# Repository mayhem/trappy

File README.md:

# trappy
Trappy, the mobile hippie trap

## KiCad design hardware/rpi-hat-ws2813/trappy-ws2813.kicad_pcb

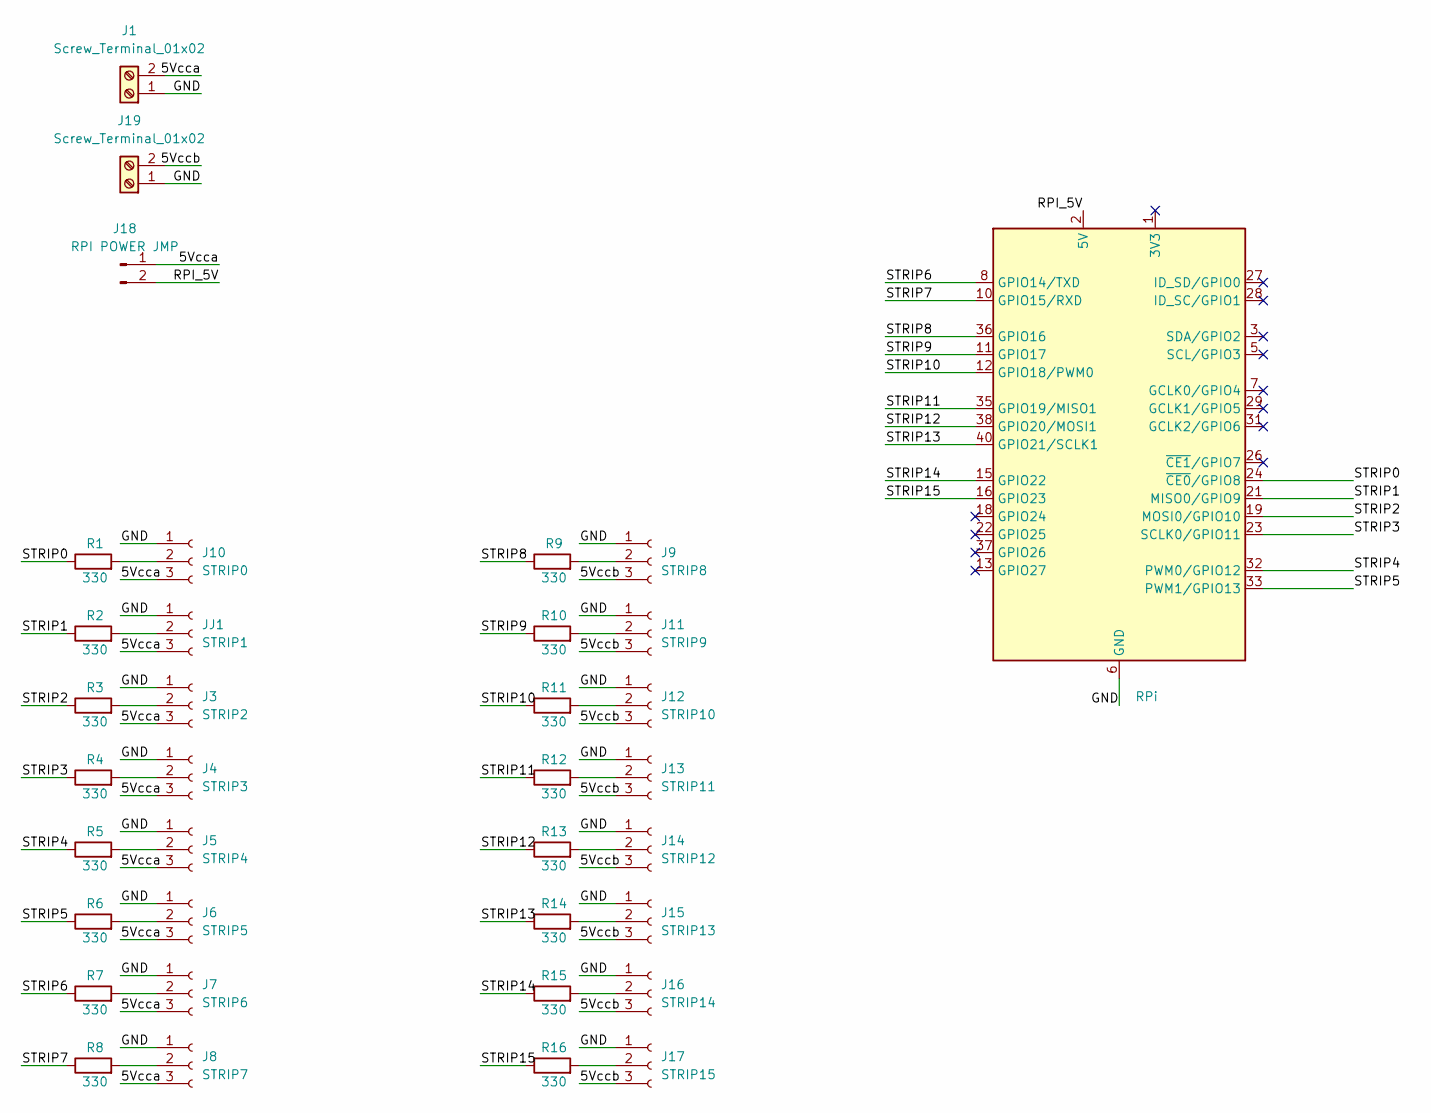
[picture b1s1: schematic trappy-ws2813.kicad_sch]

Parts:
J1, J19: Screw_Terminal_01x02; TerminalBlock_bornier-2_P5.08mm
J2: RPi; PinHeader_2x20_P2.54mm_Vertical
J3: STRIP2; JST_EH_B3B-EH-A_1x03_P2.50mm_Vertical
J4: STRIP3; JST_EH_B3B-EH-A_1x03_P2.50mm_Vertical
J5: STRIP4; JST_EH_B3B-EH-A_1x03_P2.50mm_Vertical
J6: STRIP5; JST_EH_B3B-EH-A_1x03_P2.50mm_Vertical
J7: STRIP6; JST_EH_B3B-EH-A_1x03_P2.50mm_Vertical
J8: STRIP7; JST_EH_B3B-EH-A_1x03_P2.50mm_Vertical
J9: STRIP8; JST_EH_B3B-EH-A_1x03_P2.50mm_Vertical
J10: STRIP0; JST_EH_B3B-EH-A_1x03_P2.50mm_Vertical
J11: STRIP9; JST_EH_B3B-EH-A_1x03_P2.50mm_Vertical
J12: STRIP10; JST_EH_B3B-EH-A_1x03_P2.50mm_Vertical
J13: STRIP11; JST_EH_B3B-EH-A_1x03_P2.50mm_Vertical
J14: STRIP12; JST_EH_B3B-EH-A_1x03_P2.50mm_Vertical
J15: STRIP13; JST_EH_B3B-EH-A_1x03_P2.50mm_Vertical
J16: STRIP14; JST_EH_B3B-EH-A_1x03_P2.50mm_Vertical
J17: STRIP15; JST_EH_B3B-EH-A_1x03_P2.50mm_Vertical
J18: RPI POWER JMP; PinHeader_1x02_P2.54mm_Vertical
JJ1: STRIP1; JST_EH_B3B-EH-A_1x03_P2.50mm_Vertical
R1, R2, R3, R4, R5, R6, R7, R8, R9, R10, R11, R12, R13, R14, R15, R16: 330; R_0805_2012Metric

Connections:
/5Vcca: J1.2, J3.3, J4.3, J5.3, J6.3, J7.3, J8.3, J10.3, J18.1, JJ1.3
/5Vccb: J9.3, J11.3, J12.3, J13.3, J14.3, J15.3, J16.3, J17.3, J19.2
/GND: J1.1, J2.6 (GND), J2.9 (GND), J2.14 (GND), J2.20 (GND), J2.25 (GND), J2.30 (GND), J2.34 (GND), J2.39 (GND), J3.1, J4.1, J5.1, J6.1, J7.1, J8.1, J9.1, J10.1, J11.1, J12.1, J13.1, J14.1, J15.1, J16.1, J17.1, J19.1, JJ1.1
/RPI_5V: J2.2 (5V), J2.4 (5V), J18.2
/STRIP0: J2.24 (~CE0/GPIO8), R1.1
/STRIP1: J2.21 (MISO0/GPIO9), R2.1
/STRIP2: J2.19 (MOSI0/GPIO10), R3.1
/STRIP3: J2.23 (SCLK0/GPIO11), R4.1
/STRIP4: J2.32 (PWM0/GPIO12), R5.1
/STRIP5: J2.33 (PWM1/GPIO13), R6.1
/STRIP6: J2.8 (GPIO14/TXD), R7.1
/STRIP7: J2.10 (GPIO15/RXD), R8.1
/STRIP8: J2.36 (GPIO16), R9.1
/STRIP9: J2.11 (GPIO17), R10.1
/STRIP10: J2.12 (GPIO18/PWM0), R11.1
/STRIP11: J2.35 (GPIO19/MISO1), R12.1
/STRIP12: J2.38 (GPIO20/MOSI1), R13.1
/STRIP13: J2.40 (GPIO21/SCLK1), R14.1
/STRIP14: J2.15 (GPIO22), R15.1
/STRIP15: J2.16 (GPIO23), R16.1
unnamed: J3.2, R3.2
unnamed: J4.2, R4.2
unnamed: J5.2, R5.2
unnamed: J6.2, R6.2
unnamed: J7.2, R7.2
unnamed: J8.2, R8.2
unnamed: J9.2, R9.2
unnamed: J10.2, R1.2
unnamed: J11.2, R10.2
unnamed: J12.2, R11.2
unnamed: J13.2, R12.2
unnamed: J14.2, R13.2
unnamed: J15.2, R14.2
unnamed: J16.2, R15.2
unnamed: J17.2, R16.2
unnamed: JJ1.2, R2.2

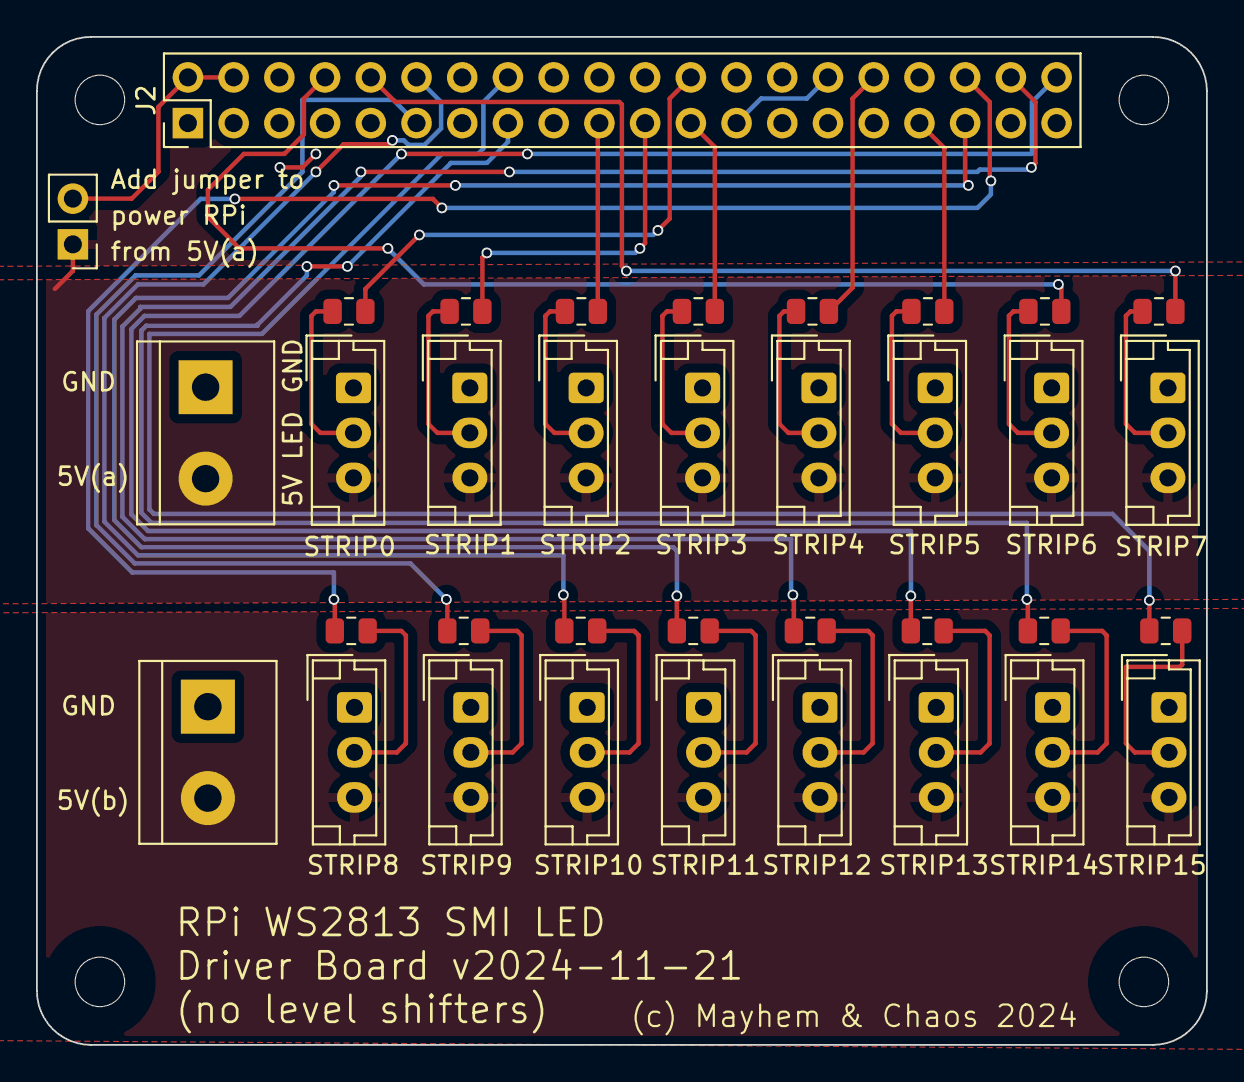
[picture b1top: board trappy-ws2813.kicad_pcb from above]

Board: 2 copper layers, 65.0 x 56.0 mm, 36 parts (0 on the bottom side), 36 nets.

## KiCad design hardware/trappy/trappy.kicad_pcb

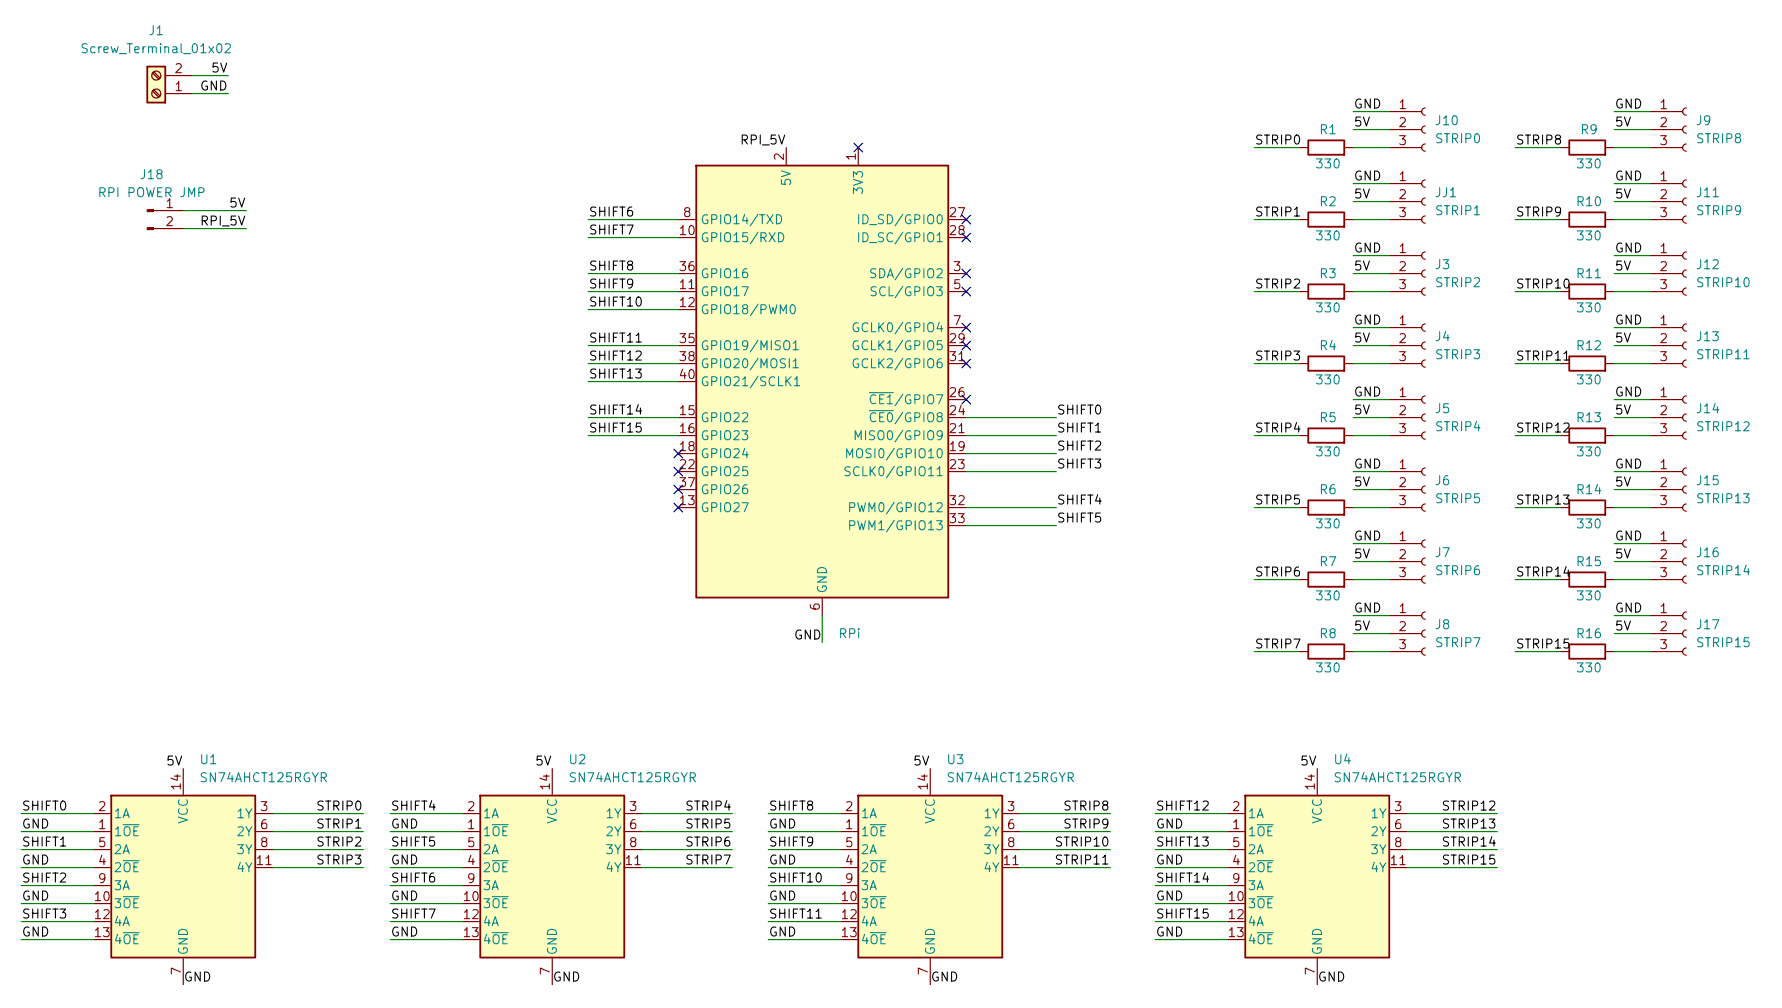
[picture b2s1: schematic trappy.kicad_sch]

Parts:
J1: Screw_Terminal_01x02; TerminalBlock_WAGO_236-102_1x02_P5.00mm_45Degree
J2: RPi; PinHeader_2x20_P2.54mm_Vertical
J3: STRIP2; JST_EH_B3B-EH-A_1x03_P2.50mm_Vertical
J4: STRIP3; JST_EH_B3B-EH-A_1x03_P2.50mm_Vertical
J5: STRIP4; JST_EH_B3B-EH-A_1x03_P2.50mm_Vertical
J6: STRIP5; JST_EH_B3B-EH-A_1x03_P2.50mm_Vertical
J7: STRIP6; JST_EH_B3B-EH-A_1x03_P2.50mm_Vertical
J8: STRIP7; JST_EH_B3B-EH-A_1x03_P2.50mm_Vertical
J9: STRIP8; JST_EH_B3B-EH-A_1x03_P2.50mm_Vertical
J10: STRIP0; JST_EH_B3B-EH-A_1x03_P2.50mm_Vertical
J11: STRIP9; JST_EH_B3B-EH-A_1x03_P2.50mm_Vertical
J12: STRIP10; JST_EH_B3B-EH-A_1x03_P2.50mm_Vertical
J13: STRIP11; JST_EH_B3B-EH-A_1x03_P2.50mm_Vertical
J14: STRIP12; JST_EH_B3B-EH-A_1x03_P2.50mm_Vertical
J15: STRIP13; JST_EH_B3B-EH-A_1x03_P2.50mm_Vertical
J16: STRIP14; JST_EH_B3B-EH-A_1x03_P2.50mm_Vertical
J17: STRIP15; JST_EH_B3B-EH-A_1x03_P2.50mm_Vertical
J18: RPI POWER JMP; PinHeader_1x02_P2.54mm_Vertical
JJ1: STRIP1; JST_EH_B3B-EH-A_1x03_P2.50mm_Vertical
R1, R2, R3, R4, R5, R6, R7, R8, R9, R10, R11, R12, R13, R14, R15, R16: 330; R_0805_2012Metric
U1, U2, U3, U4: SN74AHCT125RGYR; Texas_S-PVQFN-N14

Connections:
/5V: J1.2, J3.2, J4.2, J5.2, J6.2, J7.2, J8.2, J9.2, J10.2, J11.2, J12.2, J13.2, J14.2, J15.2, J16.2, J17.2, J18.1, JJ1.2, U1.14 (VCC), U2.14 (VCC), U3.14 (VCC), U4.14 (VCC)
/GND: J1.1, J2.6 (GND), J2.9 (GND), J2.14 (GND), J2.20 (GND), J2.25 (GND), J2.30 (GND), J2.34 (GND), J2.39 (GND), J3.1, J4.1, J5.1, J6.1, J7.1, J8.1, J9.1, J10.1, J11.1, J12.1, J13.1, J14.1, J15.1, J16.1, J17.1, JJ1.1, U1.1 (1~OE), U1.4 (2~OE), U1.7 (GND), U1.10 (3~OE), U1.13 (4~OE), U2.1 (1~OE), U2.4 (2~OE), U2.7 (GND), U2.10 (3~OE), U2.13 (4~OE), U3.1 (1~OE), U3.4 (2~OE), U3.7 (GND), U3.10 (3~OE), U3.13 (4~OE), U4.1 (1~OE), U4.4 (2~OE), U4.7 (GND), U4.10 (3~OE), U4.13 (4~OE)
/RPI_5V: J2.2 (5V), J2.4 (5V), J18.2
/SHIFT0: J2.24 (~CE0/GPIO8), U1.2 (1A)
/SHIFT1: J2.21 (MISO0/GPIO9), U1.5 (2A)
/SHIFT2: J2.19 (MOSI0/GPIO10), U1.9 (3A)
/SHIFT3: J2.23 (SCLK0/GPIO11), U1.12 (4A)
/SHIFT4: J2.32 (PWM0/GPIO12), U2.2 (1A)
/SHIFT5: J2.33 (PWM1/GPIO13), U2.5 (2A)
/SHIFT6: J2.8 (GPIO14/TXD), U2.9 (3A)
/SHIFT7: J2.10 (GPIO15/RXD), U2.12 (4A)
/SHIFT8: J2.36 (GPIO16), U3.2 (1A)
/SHIFT9: J2.11 (GPIO17), U3.5 (2A)
/SHIFT10: J2.12 (GPIO18/PWM0), U3.9 (3A)
/SHIFT11: J2.35 (GPIO19/MISO1), U3.12 (4A)
/SHIFT12: J2.38 (GPIO20/MOSI1), U4.2 (1A)
/SHIFT13: J2.40 (GPIO21/SCLK1), U4.5 (2A)
/SHIFT14: J2.15 (GPIO22), U4.9 (3A)
/SHIFT15: J2.16 (GPIO23), U4.12 (4A)
/STRIP0: R1.1, U1.3 (1Y)
/STRIP1: R2.1, U1.6 (2Y)
/STRIP2: R3.1, U1.8 (3Y)
/STRIP3: R4.1, U1.11 (4Y)
/STRIP4: R5.1, U2.3 (1Y)
/STRIP5: R6.1, U2.6 (2Y)
/STRIP6: R7.1, U2.8 (3Y)
/STRIP7: R8.1, U2.11 (4Y)
/STRIP8: R9.1, U3.3 (1Y)
/STRIP9: R10.1, U3.6 (2Y)
/STRIP10: R11.1, U3.8 (3Y)
/STRIP11: R12.1, U3.11 (4Y)
/STRIP12: R13.1, U4.3 (1Y)
/STRIP13: R14.1, U4.6 (2Y)
/STRIP14: R15.1, U4.8 (3Y)
/STRIP15: R16.1, U4.11 (4Y)
unnamed: J3.3, R3.2
unnamed: J4.3, R4.2
unnamed: J5.3, R5.2
unnamed: J6.3, R6.2
unnamed: J7.3, R7.2
unnamed: J8.3, R8.2
unnamed: J9.3, R9.2
unnamed: J10.3, R1.2
unnamed: J11.3, R10.2
unnamed: J12.3, R11.2
unnamed: J13.3, R12.2
unnamed: J14.3, R13.2
unnamed: J15.3, R14.2
unnamed: J16.3, R15.2
unnamed: J17.3, R16.2
unnamed: JJ1.3, R2.2

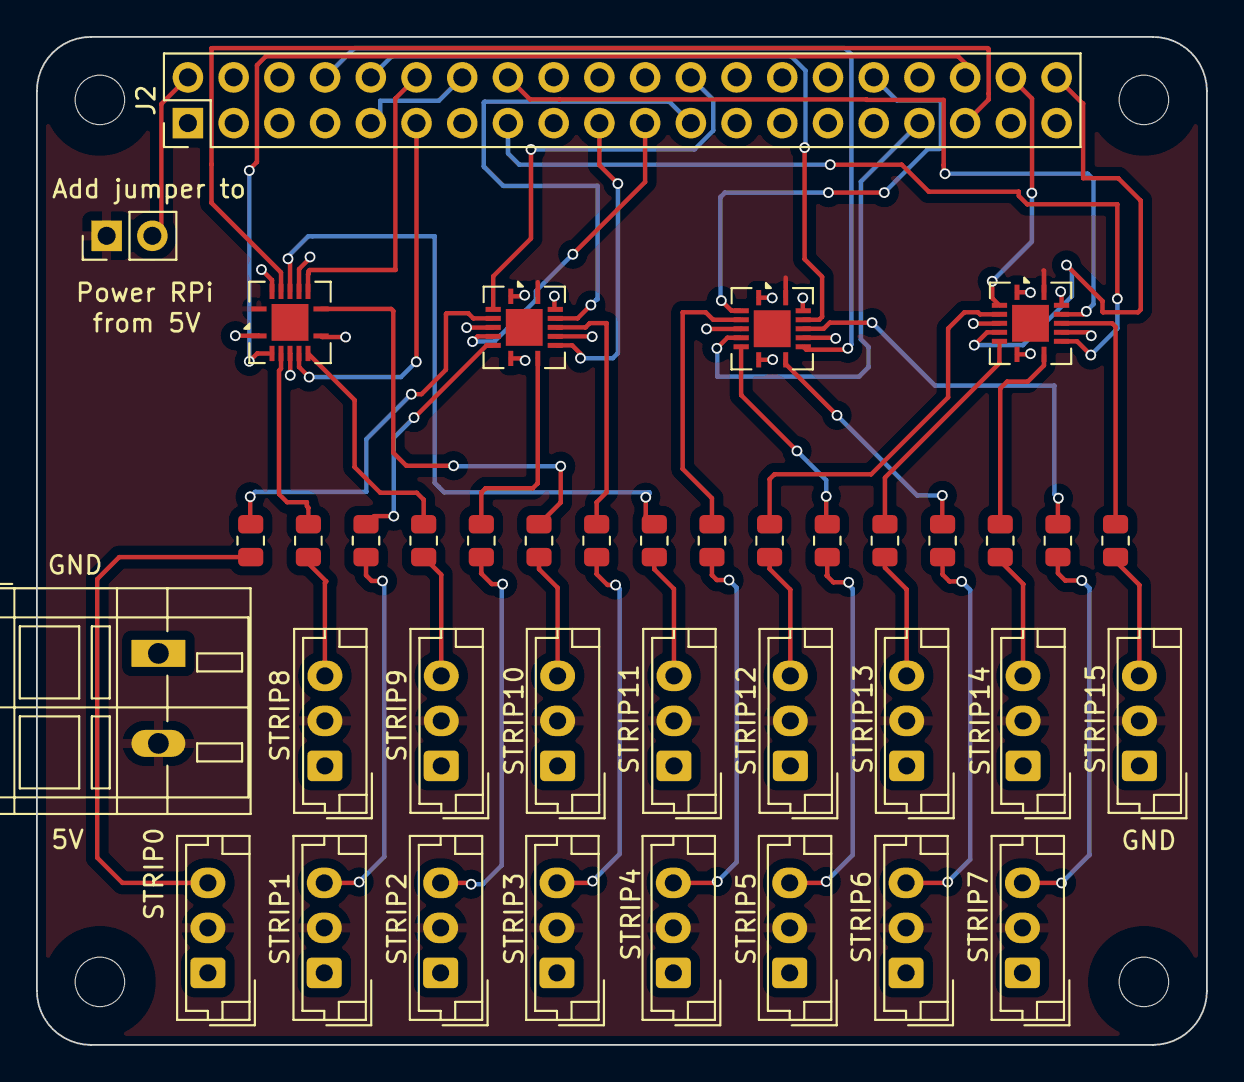
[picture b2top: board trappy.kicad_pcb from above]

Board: 2 copper layers, 65.0 x 56.0 mm, 39 parts (0 on the bottom side), 51 nets.

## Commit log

2024-04-12 First commit!
2024-04-12 New driver is working!
2024-04-12 Add in
2024-04-13 Generally working, but still strangely slow
2024-04-14 Fully debugged test case in place!
2024-04-22 Gateway code
2024-04-22 Gradients work
2024-04-22 Basic hippie trap operational. Not great, but working.
2024-04-24 The shift function works and is debugged.
2024-04-25 New system finally debugged
2024-04-25 MOre stuff is working!
2024-05-01 Break into more modules
2024-05-01 Gradient palletes are working, everything finally debugged.
2024-05-07 Finally adding python effects!
2024-05-07 Interim checkin
2024-05-07 NERDVANA!
2024-05-07 Loking really promising!
2024-05-08 scoller ported and working
2024-05-08 Starting work on a gradient scroller
2024-05-09 Gradient chase working
2024-05-09 More gradients
2024-05-09 More tweaks prior to vidalia
2024-05-10 Make gradient scroller go inward
2024-05-10 Improve gradient scroller
2024-05-16 Start work on hardware for trappy
2024-05-17 Looking pretty good!
2024-05-22 Check in latest trappy board, awaiting the board from china
2024-05-28 Fix silkscreen
2024-06-04 Changes from vidalia
2024-07-09 Add APC mini rainbow keypad setting.
2024-07-10 Now for a workable baseline
2024-07-10 Color selection working, custom colors being stored.
2024-07-11 HSV implemented in a cool way, but horrible ux
2024-07-11 HSV almost working. again.
2024-07-11 HSV is actually working, time to connec to the hippie trap
2024-07-12 time to connect to trappy!
2024-07-12 APC connected, now to drive patterns
2024-07-14 APC is controlling things!
2024-08-05 gamma correction improvements
2024-08-24 Now using prod smileds!
2024-08-25 REwriting the scroller guts
2024-08-25 A much improved gradient scroller is done.
2024-08-25 forward and reverse now work
2024-08-25 Speed control is sloppily implemented
2024-08-27 Dynamic gamma correction implemented!
2024-08-27 Clearing custom colors works
2024-08-27 Making great UI progress
2024-08-27 Getting snazzy
2024-08-27 Really coming together now!
2024-08-28 Drop duplicate events for a more responsive UI
2024-08-28 Some bugs remain, but everything is improving
2024-08-29 Particle system is cool and working!
2024-08-29 Looking pretty with max particles
2024-08-29 direction implemented
2024-08-29 Moved speed and direction setting to base effect class
2024-08-29 Instant colors -> instant hit!
2024-08-29 Get the checkerboard back in, but still buggy in live color changes
2024-08-30 Two gripes fixed
2024-09-01 Fix minor crash
2024-09-01 Particle count slider now works correctly.
2024-09-05 Add function to wait for apc mini to be connected
2024-09-05 Start stop trappy based on APC being plugged in
2024-09-08 Add sparkle effect
2024-09-08 Simplfying fader handling to be more central in effect base class
2024-09-08 Sparkles now can set the fade constant
2024-09-08 Add sweep pattern. a bit confusing and lacking color interaction
2024-09-09 Move delay logic to effect base class
2024-09-09 Add sprite support to particle system. It doesn't feel intuitive, but its not bad either.
2024-09-09 Making the particle system much more complex -- this will be really cool!
2024-09-10 Light up track and scene buttons
2024-10-20 Paging of screens implemented
2024-10-20 Getting closer to having lots of effects options!
2024-10-20 Getting fun!
2024-10-20 Support for effects screen and variant selection is working!
2024-10-20 Make the first variant suck less
2024-10-24 improve render_led to allow both directions. other simplifications.
2024-10-24 Minor improvements here and there
2024-10-24 Three distinct dot effects, done!
2024-11-06 Try a new easier to use gradient
2024-11-12 Sweep pattern is now not awful
2024-11-12 Just messing around, will find something good soon
2024-11-12 Sweep no longer sucks!
2024-11-18 Add rainbow sweep
2024-11-21 Add ws2813 board with improved power planes
2024-11-24 Banged out several more sweep block patterns
2024-11-27 Start adding drop-in
2024-11-27 Added brightness support
2024-11-27 Fix one crash
2024-12-29 Add pyusb
2024-12-29 Move defs.py to config.py
2024-12-29 Ignore buttons pressed for non-existent variants
2024-12-29 Change disconnect pad to exit the app. Also pressing "stop all clips" 5 times in a row, exists the app, letting the system restart the app.
2024-12-29 Fixed rainbow sweep to work with 8 or 16 strips
2024-12-29 Add strip reversing hack
2024-12-29 Fixed the last 8 mapping
2024-12-29 Sweep patterns looking great
2025-01-01 Fix 8 sweep, fail to implement radar. Moved some functions to color
2025-01-08 start working on bookmarks
2025-01-08 Implement better sleep control, and tune sparkles
2025-01-08 Interim check-in
2025-01-08 Moved effects to subdir
2025-01-08 Revamped how faders work, each screen now has its own fader setup
2025-01-08 Hue shift works. a bit silly, but still might be useful
2025-01-08 A lot of fine tuning, done!
2025-01-08 Add spiral
2025-01-08 Reverse now works for chasing dots
2025-05-02 Minor tweaks
2025-05-02 Start implementing radial velocity
2025-05-02 A circular pattern finally works!
2025-05-03 Add sparkle drop out
2025-05-03 New variant!
2025-05-03 Added two more wipe-out modes
2025-06-02 Make the center of the spiral also rotate
2025-06-11 Cleanup
2025-06-11 Add particle link support
2025-06-11 Getting refactored renderer up
2025-06-15 Links work!
2025-06-15 profile
2025-06-15 Create new gradient
2025-06-15 Gradients are working and twice as fast! a
2025-06-17 Making improvements, gradients are much faster, but particle system is slow
2025-06-19 Particle system is much faster now
2025-06-19 tweak test pattern
2025-06-23 Abandoning the overly broad idea of links. Need to simplify
2025-06-23 Simplified approach
2025-08-10 Working!
2025-09-03 Making real progress on the re-write
2025-09-05 A lot of progress for the background new particle engine
2025-09-05 Ported the chasing dots to the new generator model
2025-09-05 First cut of ported gradient scroller
2025-09-07 Gradient slider is working well enough
2025-09-07 time to play with AI
2025-09-07 First AI generated pattern
2025-09-07 And a nice first variant. This will need a lot of tweaking to look really good
2025-09-11 Making progress porting existing patterns
2025-09-11 Background rendering now fully works
2025-09-11 Ported radar function over
